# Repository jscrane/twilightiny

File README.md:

View this project on [CADLAB.io](https://cadlab.io/project/1197). 

Twilight-3
==========

Twilight with attiny85,
[Interrupted](https://github.com/jscrane/Interrupted) and
[Tiny Safe Boot](http://jtxp.org/tech/tinysafeboot_en.htm).

Hardware
--------
The layout in version [#1](https://cadlab.io/project/1197/6bfdd5cf1f4ba5d0182bede7adce6e52f376f4fe/circuit/ZWFnbGUvdHdpbGlnaHQzLmJyZA%3D%3D) is broken, 
there's a short in the power circuit. (Never ignore ERC warnings!)

Version [#2](https://cadlab.io/project/1197/2f3ed3901fa7b14418fc2b612dbf1835c0194fca/circuit/ZWFnbGUvdHdpbGlnaHQzLmJyZA%3D%3D) has been built and tested. 
Depending on the PIR sensor used, the 22k resistor is optional. If present,
it drags down the output of 
[Mini-PIRs](https://www.futurlec.com/Mini_PIR_Module.shtml) too much.

Version [#3](https://cadlab.io/project/1197/9cf4fb193adf9d36c94b128c8913e801d072b348/circuit/ZWFnbGUvdHdpbGlnaHQzLmJyZA%3D%3D) improves the layout some more
but is (so far) untested.

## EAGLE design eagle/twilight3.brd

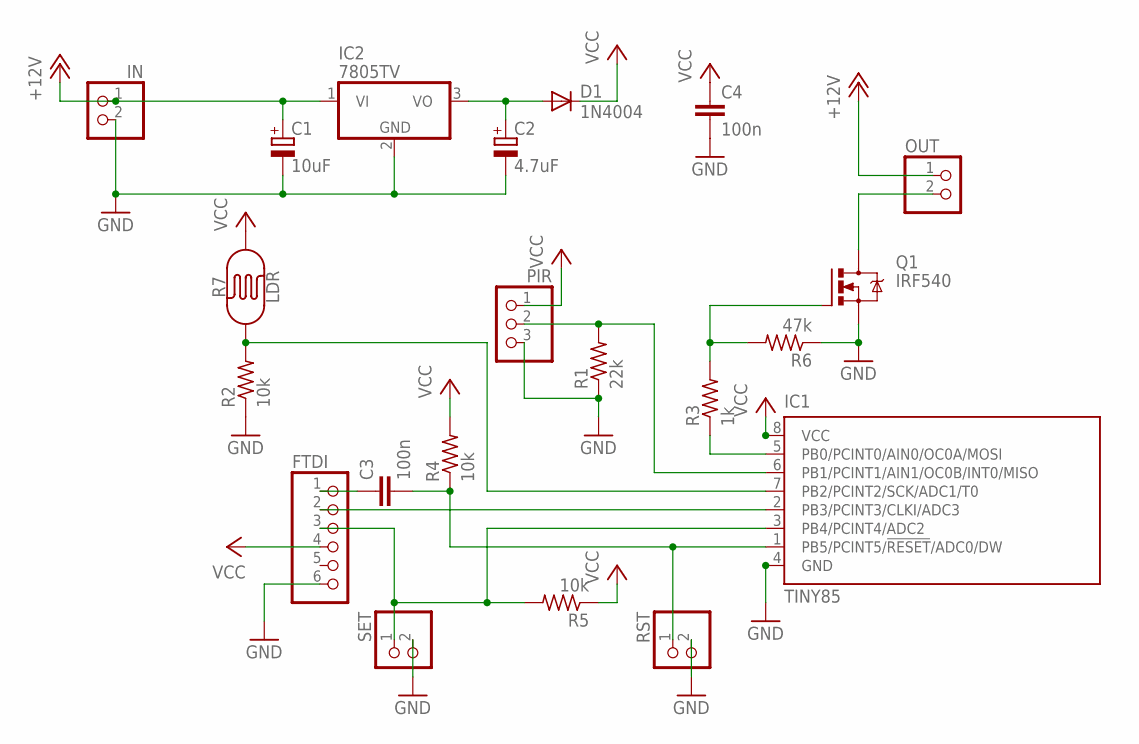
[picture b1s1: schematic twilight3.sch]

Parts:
C1: 10uF; E2-5
C2: 4.7uF; E2-5
C3, C4: 100n; C050-024X044
D1: 1N4004; DO41-10
FTDI: PINHD-1X6; 1X06
IC1: TINY85; DIL08
IC2: 7805TV; TO220V
IN: PINHD-1X2; 1X02
OUT: PINHD-1X2; 1X02
PIR: PINHD-1X3; 1X03
Q1: IRF540; TO220BV
R1: 22k; 0207/2V
R2, R4, R5: 10k; 0207/2V
R3: 1k; 0207/10
R6: 47k; 0207/10
R7: LDR; PHOTOCELL
RST: PINHD-1X2; 1X02
SET: PINHD-1X2; 1X02

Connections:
+12V: C1.+, IC2.1 (VI), IN.1, OUT.1
GND: C1.-, C2.-, C4.2, FTDI.6, IC1.4 (GND), IC2.2 (GND), IN.2, PIR.3, Q1.S, R1.1, R2.1, R6.1, RST.2, SET.2
GNDOUT: OUT.2, Q1.D
unnamed: FTDI.2, IC1.2 (PB3/PCINT3/CLKI/ADC3)
unnamed: FTDI.3, IC1.3 (PB4/PCINT4/ADC2), R5.2, SET.1
unnamed: C3.2, IC1.1 (PB5/PCINT5/!RESET!/ADC0/DW), R4.1, RST.1
unnamed: IC1.7 (PB2/PCINT2/SCK/ADC1/T0), R2.2, R7.1
unnamed: IC1.5 (PB0/PCINT0/AIN0/OC0A/MOSI), R3.1
unnamed: Q1.G, R3.2, R6.2
unnamed: C3.1, FTDI.1
unnamed: C2.+, D1.A, IC2.3 (VO)
unnamed: IC1.6 (PB1/PCINT1/AIN1/OC0B/INT0/MISO), PIR.2, R1.2
VCC: C4.1, D1.C, FTDI.4, IC1.8 (VCC), PIR.1, R4.2, R5.1, R7.2

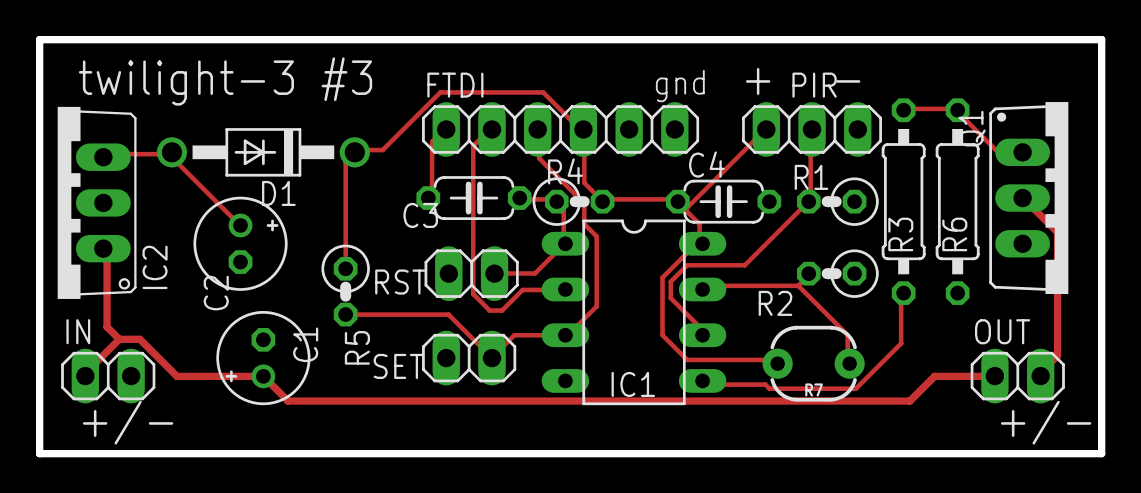
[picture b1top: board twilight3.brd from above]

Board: 2 copper layers, 59.0 x 23.0 mm, 21 parts (0 on the bottom side), 13 nets.

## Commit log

2018-06-21 Create LICENSE
2018-06-21 add eagle
2018-06-21 Backlink to CADLAB.io has been added.
2018-06-22 create issues for hardware glitches
2018-06-28 fix issues #2, #3 and #4
2018-09-07 gerbers
2018-10-21 improve labelling
2018-10-23 changing resistor sizes and orientations; move ldr to edge of board
2018-10-25 adding bypass capacitor
2018-10-25 add reset header
2018-10-26 minor update
2018-10-26 docs
2018-10-26 change orientation

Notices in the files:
eagle/twilight3.brd:
(c) 2018 steve
parts and their libraries:
SparkFun-Sensors: Licensing: Creative Commons ShareAlike 4.0 International - https://creativecommons.org/licenses/by-sa/4.0
